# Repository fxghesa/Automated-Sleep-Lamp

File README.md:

# Automated-Sleep-Lamp
Automated Sleep Lamp [PCB design only]

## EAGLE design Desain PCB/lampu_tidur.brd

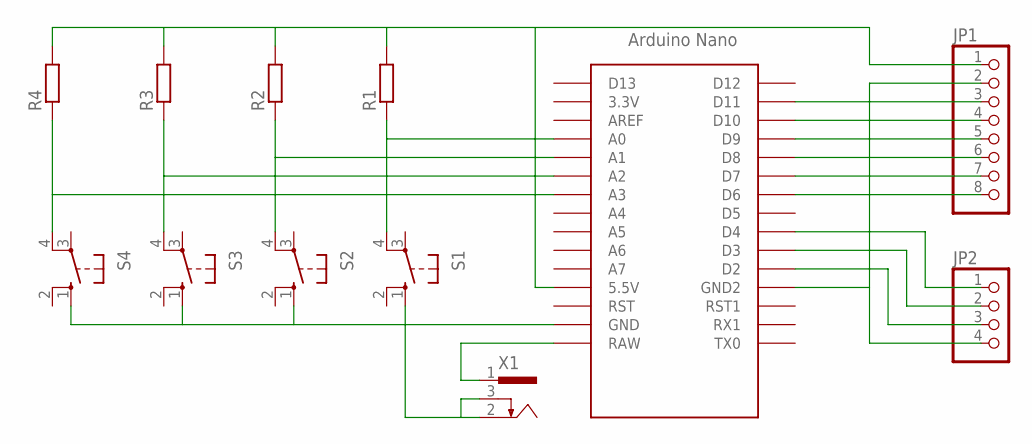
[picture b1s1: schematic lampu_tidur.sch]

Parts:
JP1: PINHD-1X8; 1X08
JP2: PINHD-1X4; 1X04
R1, R2, R3, R4: R-EU_0204/7; 0204/7
S1, S2, S3, S4: 10-XX; B3F-10XX
U$1: NANO
X1: 733980-62

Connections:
unnamed: JP1.1, R1.2, R2.2, R3.2, R4.2, U$1.5V (5.5V)
unnamed: R1.1, S1.4 (P1), U$1.A0
unnamed: S1.1 (S), S2.1 (S), S3.1 (S), S4.1 (S), U$1.GND, X1.2, X1.3
unnamed: R2.1, S2.4 (P1), U$1.A1
unnamed: U$1.RAW, X1.1
unnamed: R3.1, S3.4 (P1), U$1.A2
unnamed: R4.1, S4.4 (P1), U$1.A3
unnamed: JP1.8, U$1.D6
unnamed: JP1.7, U$1.D7
unnamed: JP1.6, U$1.D8
unnamed: JP1.5, U$1.D9
unnamed: JP1.4, U$1.D10
unnamed: JP2.1, U$1.D4
unnamed: JP2.2, U$1.D3
unnamed: JP2.3, U$1.D2
unnamed: JP1.2, JP2.4, U$1.GND1 (GND2)
unnamed: JP1.3, U$1.D11

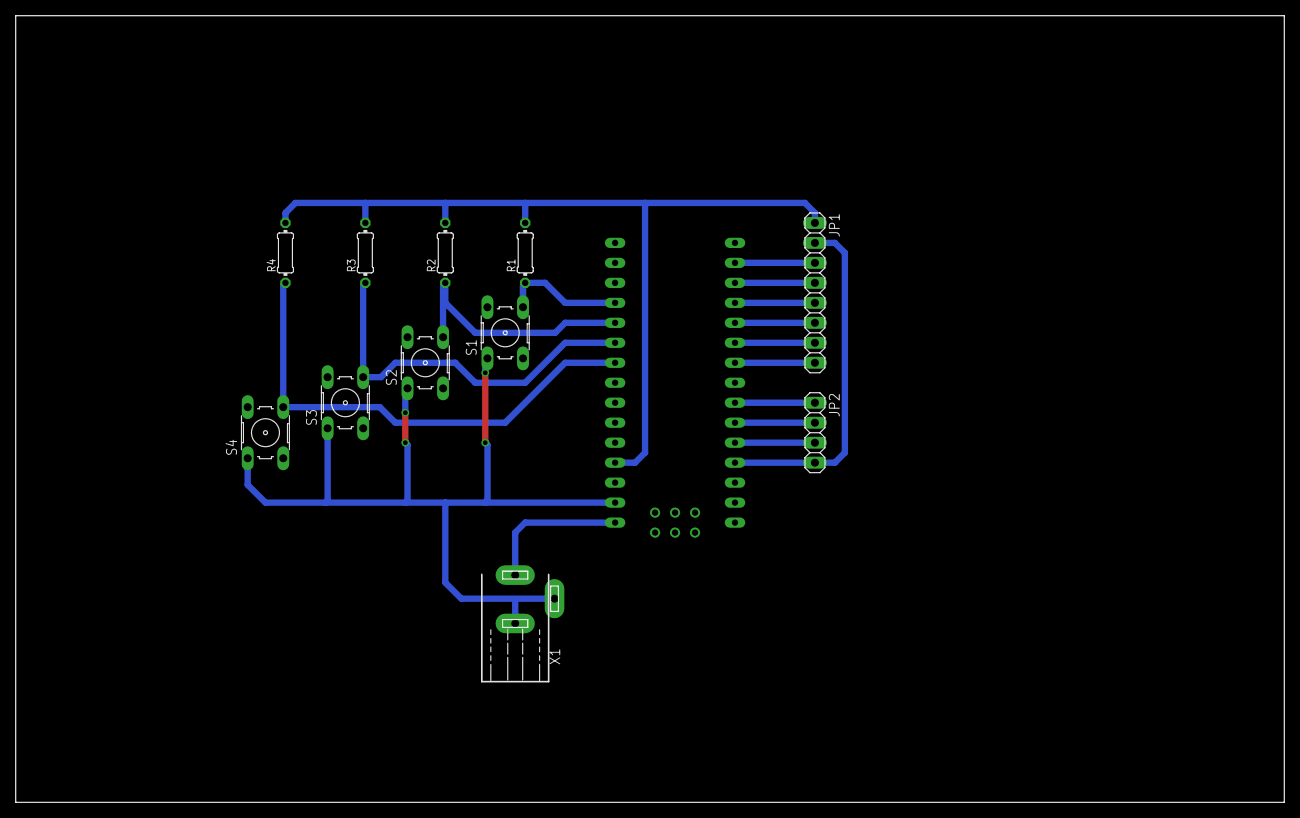
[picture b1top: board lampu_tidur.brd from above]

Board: 2 copper layers, 161.3 x 100.0 mm, 12 parts (0 on the bottom side), 17 nets.

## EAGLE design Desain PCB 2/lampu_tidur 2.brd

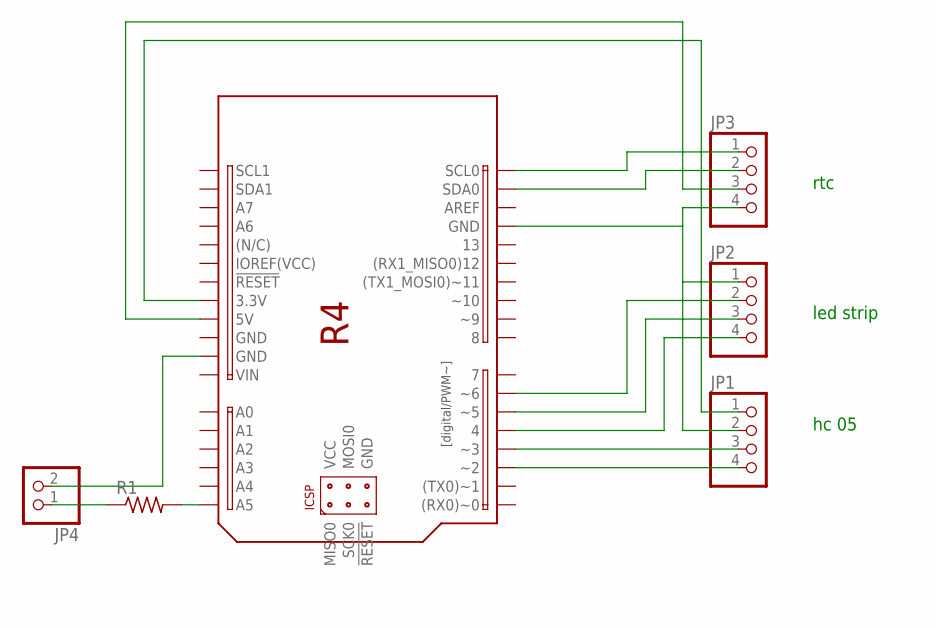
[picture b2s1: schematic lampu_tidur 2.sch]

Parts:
JP1, JP2, JP3: PINHD-1X4; 1X04
JP4: PINHD-1X2; 1X02
PCB1: R4-SHIELD
R1: R-US_0207/7; 0207/7

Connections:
unnamed: JP1.4, PCB1.2 (~2)
unnamed: JP1.3, PCB1.3 (~3)
unnamed: JP1.1, PCB1.3.3V
unnamed: JP1.2, JP2.1, JP3.4, PCB1.GND@3 (GND)
unnamed: JP2.4, PCB1.4
unnamed: JP2.3, PCB1.5 (~5)
unnamed: JP2.2, PCB1.6 (~6)
unnamed: JP3.1, PCB1.SCL (SCL0)
unnamed: JP3.2, PCB1.SDA (SDA0)
unnamed: JP3.3, PCB1.5V
unnamed: JP4.2, PCB1.GND@1 (GND)
unnamed: PCB1.A5, R1.2
unnamed: JP4.1, R1.1

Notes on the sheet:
rtc
led strip
hc 05

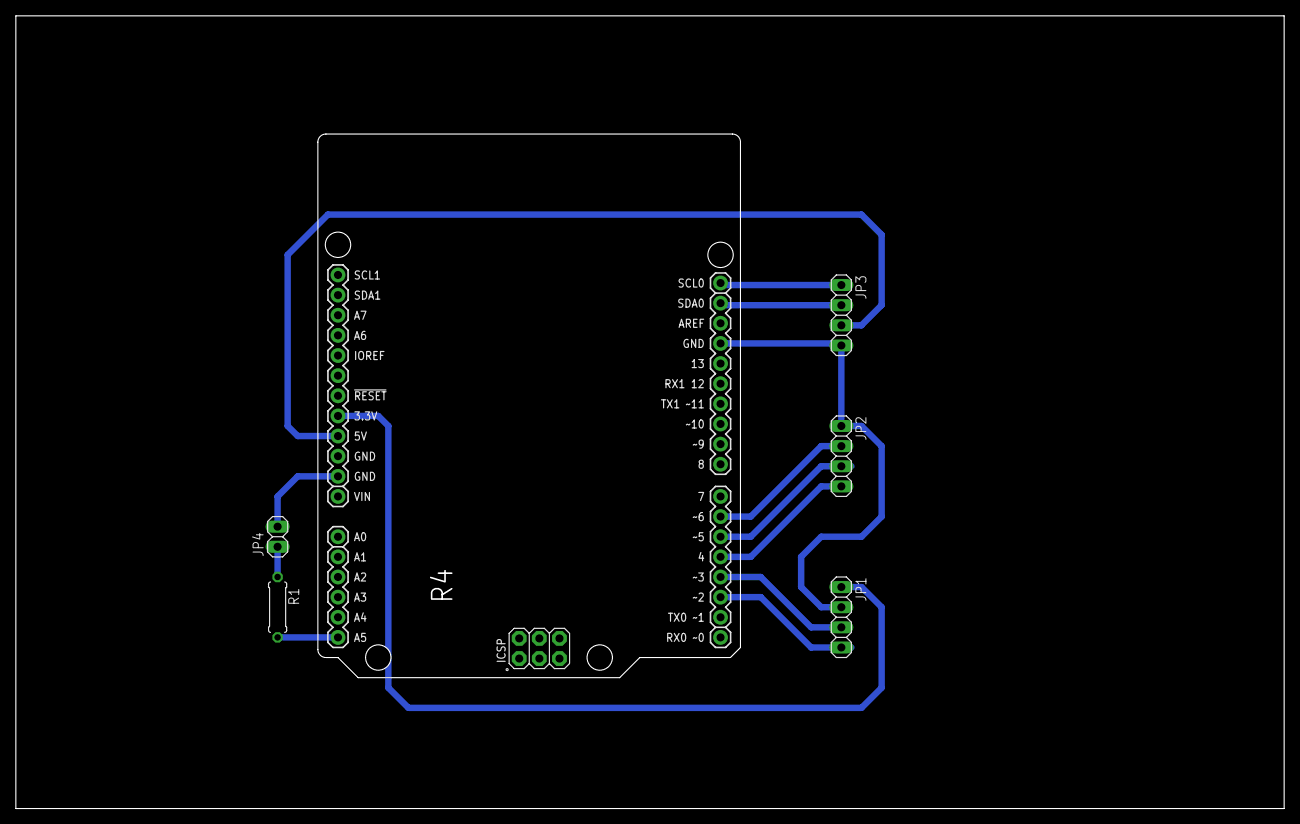
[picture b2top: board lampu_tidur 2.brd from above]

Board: 2 copper layers, 160.0 x 100.0 mm, 6 parts (0 on the bottom side), 13 nets.

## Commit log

2020-01-19 Init
